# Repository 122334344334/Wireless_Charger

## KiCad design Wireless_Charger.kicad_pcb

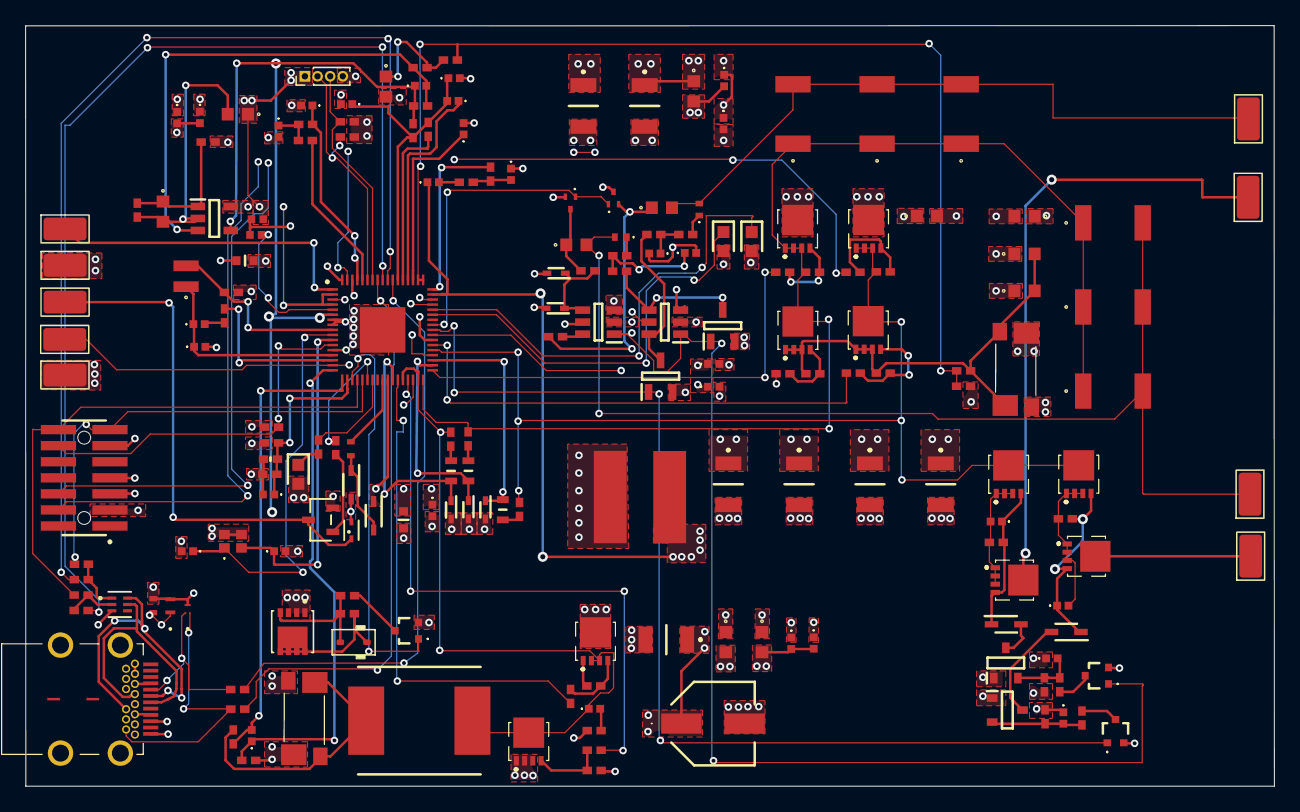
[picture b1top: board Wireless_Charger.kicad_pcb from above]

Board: 4 copper layers, 98.7 x 60.1 mm, 189 parts (0 on the bottom side), 120 nets.

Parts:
C100: 100nF; CAPC1005X55N
C101, C102: 10µF; GCM32ER71E106KA57L
C104: 33nF; C0603
C200, C239: NP; C0402C104J4RACTU
C201, C235: 4.7UF; CAPC1005X70N
C202: 470NF; CAPC1005X55N
C203, C207, C210, C217, C218, C219, C220, C226, C236, C237: 100NF; C0402C104J4RACTU
C204, C206: 10UF; GRM18x
C208, C240, C310, C313, C402, C423: 1NF; C0402C104J4RACTU
C209, C231: 5.6NF; C0603
C211, C212, C213: 330NF; CAPC1608X80N
C214, C215, C216, C227, C314, C315, C418, C425: 10NF; C0402C104J4RACTU
C221, C222: 8.2PF; C0402C104J4RACTU
C228, C229: 33PF; C0402C104J4RACTU
C238: 1UF; C0402C104J4RACTU
C241, C242, C243, C302, C309, C400, C431, C432, C433: 100NF; C0603
C304, C419, C420, C421, C422: 10UF; GCM32ER71E106KA57L
C308: 47UF; EEE0JA331XP
C407, C408, C410, C412: 100NF; C4532_Commercial
C409, C415: 47NF; C4532_Commercial
CC220, CC230: 1NF; GRM15x
D100: ESDA25P35-1U1M; QFN1610_STM-L
D102: ECMF02-2AMX6; QFN-6L_STM-L
D103: ESDALC6V1M3; SOT_C6V1M3_STM-L
D104: BAT30KFILM; SOD-523_STM-L
D200, D201: RB541VM-40FHTE-17; SODFL2512X90N
D202: RED; LEDC1608X80N
D203, D209: GREEN; LEDC1608X80N
D204, D205, D206, D207, D208: BAT54KFILM; SODFL1608X70N
D400: 10V; D_SOD-323
D401, D402: 1N4148WS-7-F; SOD2513X120N
J100: 632723300011
J101: FTSH-107-01-L-DV-K-A; SAMTEC_FTSH-107-01-L-DV-K-A
J201: 0022232041; PinHeader_1x04_P1.00mm_Vertical
L200: 10uH; VLS2520
L300: 3.3uH; INDPM9785X400N
L400: 1uH; WE-TPC_682392
Q100: NTR4003NT1G; SOT-23-3_1P4X3P040_ONS-L
Q200, Q203: NTK3134NT1G
Q201, Q202: 2N7002; SOT95P280X125-3N
Q300, Q301, Q400, Q401, Q402, Q403, Q406, Q407, Q408, Q409: STL20N6F7
Q404: DMP3017SFGQ-7; TRANS_DMP3017SFGQ-7
Q405: PDTC114EU,115; PDTC114EU115
Q410, Q413: NPN; PDTC114EU115
Q411, Q412: BC856BMTF; SOT95P240X114-3N
R100, R103: NP; RESC1005X40N
R101, R102: 10 R; RESC1005X40N
R106, R107, R108: 0 R; RESC1005X40N
R200, R220, R221, R301, R302, R400, R403, R404, R407: 0R; RESC1005X40N
R201, R219, R305, R306, R307: 10R; RESC1005X40N
R202, R204, R208, R209, R229, R303, R304, R411, R412, R413, R414, R415, R416, R421, R423, R425: 10K; RESC1005X40N
R203: 150K; RESC1005X40N
R206: 47K; THRMC1005X55N
R207, R223, R422, R428: 47K; RESC1005X40N
R212, R225, R226: 2.2R; RESC1005X40N
R217: 470K; RESC1005X37N
R218, R222: 3.3K; RESC1005X40N
R224: RC0402JR-070RL; RESC1005X40N
R227, R228, R237: 4.7K; RESC1005X40N
R230, R234: 330K; RESC1005X37N
R231: 1.2K; RESC1005X37N
R232: 9.1K; RESC1005X37N
R233: 5.6K; RESC1005X37N
R235, R236: 100R; RESC1005X40N
R300, R408: 0.010R; Y14870R01000B9R
R410: 100K; RESC1005X40N
TP100, TP101, TP102, TP103: TestPoint; TestPoint_Keystone_5015_Micro_Mini
TP200: TestPoint_Keystone_5015_Micro_Mini
TP400, TP401, TP403, TP404: 1; TestPoint_Keystone_5015_Micro_Mini
U200: STWBC2-HP; QFN40P800X800X100-69N-D
U201, U202: STG719STR; SOT95P280X145-6N
U203: LMV321ILT; SOT95P280X145-5N
Y200: NX2016SA-16MHZ; NX2016SA16MHZEXS00ACS06655

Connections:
1V8: C235.1, U200.5 (LDO_1V8)
3V3: C201.1, C243.1, D209.2 (A), J101.03, J201.1, R202.1, R203.1, R227.1, R228.1, U200.2 (LDO_3V3), U200.4 (MCU_3V3), U203.5 (VCC)
/BRIDGE_ISNS_N: R221.1, R224.1, R231.2, U200.52 (BRG_ISNS_M), U200.53 (BRG_ISNS_P)
/DC-DC/VBRIDGE: D400.1 (K), Q404.5, Q404.6, Q404.7, Q404.8, R410.2
/DCDC_SHORT: Q405.1 (B), U200.20 (SPI_CLK)
/FAN: R108.1, U200.23 (SPI_MISO)
/GD_HS1: R301.1, U200.29 (HS1_GD)
/GD_HS2: R400.2, U200.35 (HS2_GD)
/GD_HS3: R403.2, U200.38 (HS3_GD)
/GD_LS1: R302.1, U200.31 (LS1_GD)
/GD_LS2: R404.2, U200.32 (LS2_GD)
/GD_LS3: R407.2, U200.40 (LS3_GD)
/I2C_SCL: J201.2, R227.2, U200.63 (I2C_SCL)
/I2C_SDA: J201.3, R228.2, U200.62 (I2C_SDA)
/LED1: D203.1 (K), U200.46 (LED1)
/LED2: D202.1 (K), U200.47 (LED2)
/LED3: R237.2, U200.24 (SPI_MOSI)
/NRESET: J101.12, R202.2, U200.12 (NRST)
/QF_DRV: U200.66 (QF_DRV), U201.5 (D)
/QF_SHORT: Q200.1 (G), Q203.1 (G), U200.44 (GPIO_DR2)
/RING_NODE1: C209.2, C407.2, C408.2, C409.2, CC220.2, TP401.1
/RING_NODE2: C231.2, C410.2, C412.2, C415.2, CC230.2, TP404.1
/RING_SNS: U200.67 (RNG_SNS), U202.5 (D)
/SWCLK: J101.06, U200.49 (SWCLK)
/SWDIO: J101.04, U200.48 (SWDIO)
/SW_HS1: C313.1, L300.1, Q300.2 (S), Q300.3 (S), Q301.5 (D), R226.2, U200.30 (HS1_SW), U200.33 (DCDC_SNS)
/SW_HS2: C407.1, C408.1, C409.1, C410.1, C412.1, C415.1, Q400.1 (S), Q400.2 (S), Q400.3 (S), Q402.5 (D), R225.2, R414.2, U200.34 (HS2_SW)
/SW_HS3: Q401.1 (S), Q401.2 (S), Q401.3 (S), Q403.5 (D), Q406.5 (D), Q409.5 (D), R212.2, R412.1, U200.39 (HS3_SW)
/TANK1_ON: C418.1, D401.1 (K), Q406.4 (G), Q407.4 (G), R422.1
/TANK1_SEL: Q202.1 (G), Q410.1 (B), U200.42 (GPIO_DR0), U201.1 (IN), U202.1 (IN)
/TANK1_SW: C418.2, Q406.1 (S), Q406.2 (S), Q406.3 (S), Q407.1 (S), Q407.2 (S), Q407.3 (S), R422.2
/TANK2_ON: C425.1, D402.1 (K), Q408.4 (G), Q409.4 (G), R428.1
/TANK2_SEL: Q201.1 (G), Q413.1 (B), U200.43 (GPIO_DR1)
/TANK2_SW: C425.2, Q408.1 (S), Q408.2 (S), Q408.3 (S), Q409.1 (S), Q409.2 (S), Q409.3 (S), R428.2
/UART_RX: J101.13, R103.2, U200.22 (UART_RX)
/UART_TX: J101.14, R100.2, U200.21 (UART_TX)
/USB_CC1: R107.1, U200.58 (CC1)
/USB_CC2: R106.2, U200.61 (CC2)
/USB_D+: D102.6 (D+), J100.A6 (DP1), J100.B6 (DP2)
/USB_D-: D102.5 (D-), J100.A7 (DN1), J100.B7 (DN2)
/USB_DM: R101.2, U200.60 (USB_DM)
/USB_DP: R102.2, U200.59 (USB_DP)
/VIN_ISNS_N: C315.2, R307.1, U200.18 (VIN_ISNS_N)
/VIN_ISNS_P: C315.1, R306.1, U200.17 (VIN_ISNS_P)
Earth: C100.2, C101.2, C102.2, C104.2, C200.2, C201.2, C204.2, C206.2, C207.2, C208.1, C210.2, C214.2, C216.2, C217.2, C218.2, C219.2, C220.2, C221.2, C222.2, C226.2, C228.2, C229.2, C235.2, C236.2, C237.2, C238.2, C239.2, C241.2, C302.2, C304.2, C308.2 (-), C309.2, C310.2, C314.2, C400.1, C419.2, C420.2, C421.2, C422.2, C431.1, D100.2, D102.3 (GND), D103.3 (GND), D207.2 (A), D208.2 (A), J100.A1 (GND), J100.A12 (GND), J101.05, J101.07, J101.11, Q100.2 (SOURCE), Q200.2 (S), Q201.2 (S), Q202.2 (S), Q203.3 (D), Q301.1 (S), Q301.2 (S), Q301.3 (S), Q405.2 (E), Q410.2 (E), Q413.2 (E), R206.2, R217.2, R224.2, R304.2, R305.2, R408.3, R408.4, TP101.1, U200.7 (MCU_VSS), U200.8 (MCU_VSS1), U200.13 (PGND), U200.41 (GND_DR), U200.68 (AGND), U200.69 (GND), U201.3 (GND), U202.3 (GND), Y200.3 (CRYSTAL_2), Y200.4 (GND_2)
unnamed: C203.2, R201.2
unnamed: C208.2, R219.2, R220.1
unnamed: C211.2, R212.1
unnamed: C212.2, R225.1
unnamed: C213.2, R226.1
unnamed: C219.1, R208.2, R209.1
unnamed: C227.2, R219.1
unnamed: C228.1, R207.2, R218.1
unnamed: C229.1, R222.1, R223.2
unnamed: C241.1, R231.1, R232.2
unnamed: C313.2, R305.1
unnamed: C432.2, C433.2, Q402.1 (S), Q402.2 (S), Q402.3 (S), Q403.1 (S), Q403.2 (S), Q403.3 (S), R221.2, R408.1, R408.2, R413.2, R415.2
unnamed: CC220.1, R218.2
unnamed: CC230.1, R222.2
unnamed: D102.1 (D+), R102.1, R103.1
unnamed: D102.2 (D-), R100.1, R101.1
unnamed: D103.1 (I/O1), J100.B5 (VCONN), R106.1
unnamed: D103.2 (I/O2), J100.A5 (CC), R107.2
unnamed: C202.1, D200.1 (K), D201.2 (A)
unnamed: C211.1, D204.1 (K), U200.37 (HS3_BT)
unnamed: C212.1, D205.1 (K), U200.36 (HS2_BT)
unnamed: C213.1, D206.1 (K), U200.28 (HS1_BT)
unnamed: D207.1 (K), D208.1 (K), R236.1, U201.4 (S1)
unnamed: D209.1 (K), R237.1
unnamed: D400.2 (A), Q404.4, R410.1, R411.2
unnamed: D401.2 (A), Q411.3 (C)
unnamed: D402.2 (A), Q412.3 (C)
unnamed: J100.A4 (VBUS), J100.A9 (VBUS1), J100.B4 (VBUS2), J100.B9 (VBUS3)
unnamed: L300.2, R300.3, R300.4, R307.2
unnamed: D104.2, Q100.3 (DRAIN), TP103.1
unnamed: Q100.1 (GATE), R108.2
unnamed: C231.1, Q200.3 (D), R236.2
unnamed: Q201.3 (D), R207.1, U202.6 (S2)
unnamed: Q202.3 (D), R223.1, U202.4 (S1)
unnamed: C209.1, Q203.2 (S), R235.2
unnamed: Q300.4 (G), R301.2, R303.1
unnamed: Q300.1 (S), R303.2
unnamed: Q301.4 (G), R302.2, R304.1
unnamed: Q400.4 (G), R400.1, R414.1
unnamed: Q401.4 (G), R403.1, R412.2
unnamed: Q402.4 (G), R404.1, R415.1
unnamed: Q403.4 (G), R407.1, R413.1
unnamed: Q405.3 (C), R411.1
unnamed: Q407.5 (D), TP400.1
unnamed: Q408.5 (D), TP403.1
unnamed: Q410.3 (C), R421.2
unnamed: C402.2, Q411.2 (E), R416.2, R421.1
unnamed: C423.2, Q412.2 (E), R423.2, R425.1
unnamed: Q413.3 (C), R425.2
unnamed: C215.2, C217.1, C218.1, R204.2, R229.1, U200.57 (BRG_FT_R)
unnamed: R204.1, U200.56 (BRG_FT_S)
unnamed: C215.1, U200.55 (BRG_IDEM)
unnamed: C214.1, U200.54 (BRG_VREF)
unnamed: R201.1, U200.15 (BUCK_BT)
unnamed: L200.2, R200.2, U200.9 (BUCK_FB)
unnamed: C200.1, C203.1, L200.1, U200.14 (BUCK_SW)
unnamed: R220.2, U200.51 (DCDC_FB)
unnamed: TP200.1, U200.1 (IRQ)
unnamed: C220.1, R209.2, U200.65 (RNG_FT_R)
unnamed: R208.1, U200.64 (RNG_FT_S)
unnamed: C216.1, R203.2, R206.1, R217.1, U200.19 (TEMPSNS)
unnamed: C202.2, U200.26 (VDOUB_SW)
unnamed: C221.1, U200.10 (XTAL_IN), Y200.1 (CRYSTAL_1)
unnamed: C222.1, U200.11 (XTAL_OUT), Y200.2 (GND_1)
unnamed: R235.1, U201.6 (S2)
unnamed: C242.2, C243.2, R233.2, U203.2 (GND)
unnamed: C242.1, R233.1, R234.1, U203.1 (IN+)
unnamed: C240.2, R230.2, R232.1, U203.3 (IN-)
unnamed: C240.1, R229.2, R230.1, U203.4 (OUTPUT)
VBRIDGE: C400.2, C419.1, C420.1, C421.1, C422.1, C431.2, C432.1, C433.1, L400.1, Q400.5 (D), Q401.5 (D)
VBUCK: C204.1, C226.1, C237.1, D104.1, D200.2 (A), D202.2 (A), D203.2 (A), J100.B1 (GND2), J100.B12 (GND3), J201.4, R200.1, TP102.1, U200.6 (VDD), U201.2 (VCC), U202.2 (VCC)
VDCDC: C227.1, C302.1, C304.1, C308.1 (+), C309.1, C310.1, C314.1, L400.2, Q300.5 (D), U200.50 (BRG_VSNS)
VDD_DR: C206.1, C236.1, C402.1, C423.1, D201.1 (K), D204.2 (A), D205.2 (A), D206.2 (A), Q411.1 (B), Q412.1 (B), R416.1, R423.1, U200.27 (VDD_DR)
VIN: C100.1, C101.1, C102.1, C104.1, C210.1, C239.1, D100.1, J100.B8 (SBU2), Q404.1, Q404.2, Q404.3, R300.1, R300.2, R306.2, TP100.1, U200.16 (VIN)
VREF: C207.1, C238.1, R234.2, U200.3 (VREF_A)

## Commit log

2025-06-11 PCB Layout V1.1
2025-06-12 Layout V1.2
2025-06-12 Layout V1.3
2025-06-13 Layout V1.4
2025-06-13 Layout V1.5
2025-06-16 Layout V1.6
2025-06-18 Layout V1.7
